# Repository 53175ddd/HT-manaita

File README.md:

# HT-manaita

Google の湯呑みキーボードの設計をもとに、それを展開して真魚板状にしました。  
派生元：<https://github.com/google/mozc-devices/tree/master/mozc-yunomi>

## 回路図

[Schematic](./img/HT-manaita.pdf)

## 画像

<div align="center">

</div>

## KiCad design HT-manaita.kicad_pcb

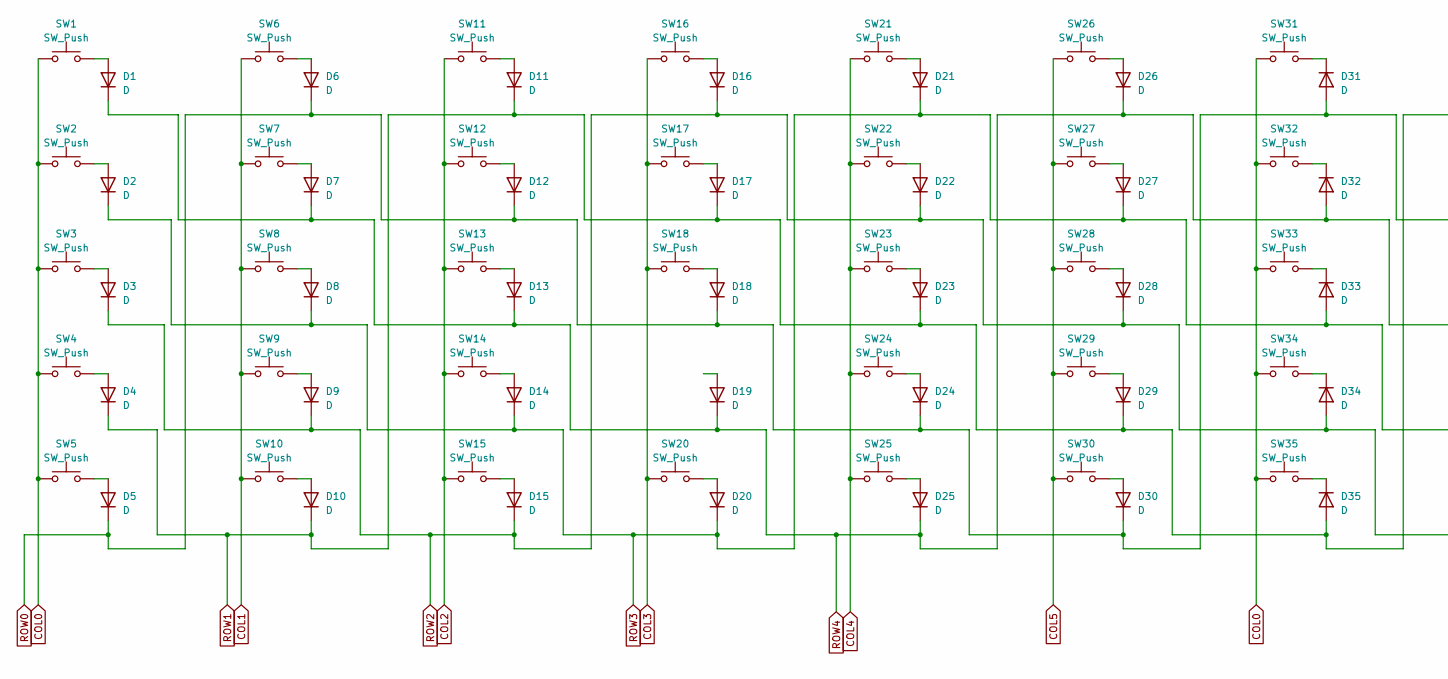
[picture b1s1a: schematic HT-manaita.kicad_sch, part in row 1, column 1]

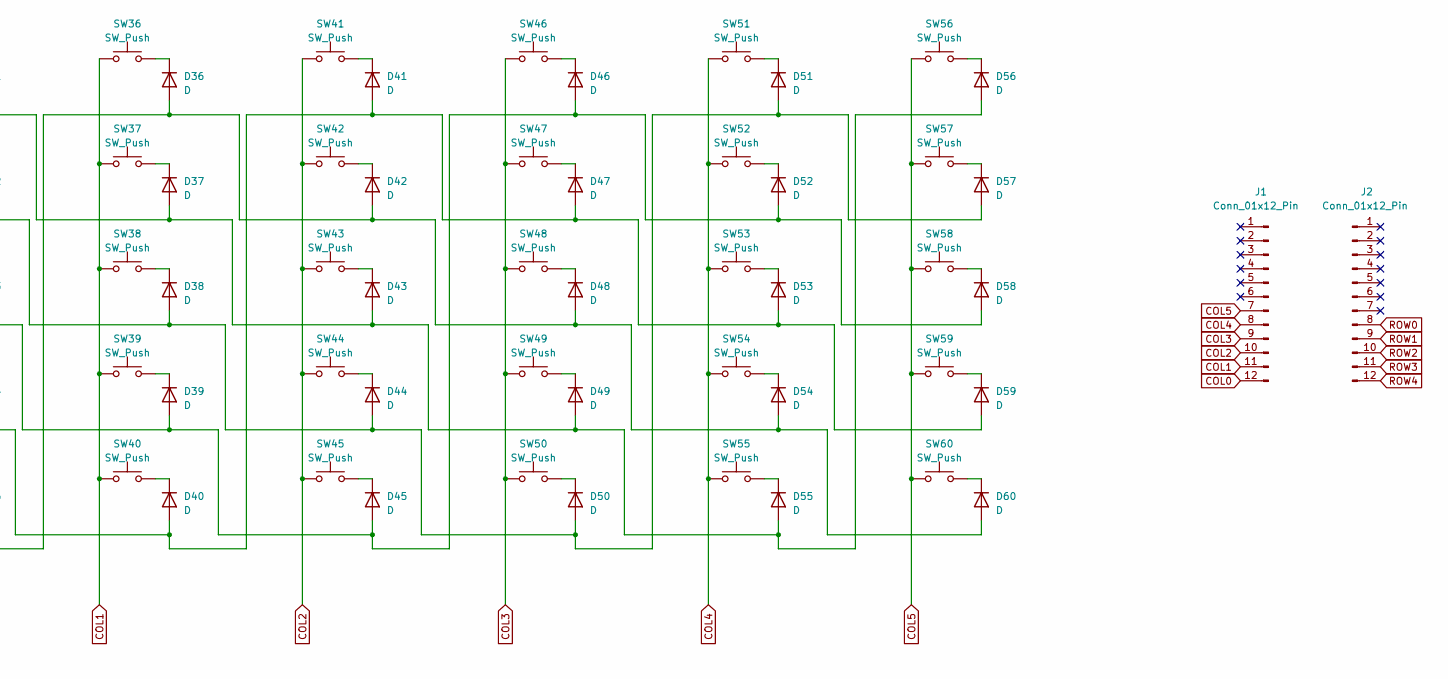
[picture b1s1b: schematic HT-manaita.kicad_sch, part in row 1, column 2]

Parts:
D1, D2, D3, D4, D5, D6, D7, D8, D9, D10, D11, D12, D13, D14, D15, D16, D17, D18, D19, D20, D21, D22, D23, D24, D25, D26, D27, D28, D29, D30, D31, D32, D33, D34, D35, D36, D37, D38, D39, D40, D41, D42, D43, D44, D45, D46, D47, D48, D49, D50, D51, D52, D53, D54, D55, D56, D57, D58, D59, D60: D; D_A-405_P10.16mm_Horizontal
J1, J2: Conn_01x12_Pin; PinHeader_1x12_P2.54mm_Vertical
SW1, SW2, SW3, SW4, SW5, SW6, SW7, SW8, SW9, SW10, SW11, SW12, SW13, SW14, SW15, SW16, SW17, SW18, SW20, SW21, SW22, SW23, SW24, SW25, SW26, SW27, SW28, SW29, SW30, SW31, SW32, SW33, SW34, SW35, SW36, SW37, SW38, SW39, SW40, SW41, SW42, SW43, SW44, SW45, SW46, SW47, SW48, SW49, SW50, SW51, SW52, SW53, SW54, SW55, SW56, SW57, SW58, SW59, SW60: SW_Push; SW_Cherry_MX_1.00u_PCB

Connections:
COL0: J1.12, SW1.1, SW2.1, SW3.1, SW4.1, SW5.1, SW31.1, SW32.1, SW33.1, SW34.1, SW35.1
COL1: J1.11, SW6.1, SW7.1, SW8.1, SW9.1, SW10.1, SW36.1, SW37.1, SW38.1, SW39.1, SW40.1
COL2: J1.10, SW11.1, SW12.1, SW13.1, SW14.1, SW15.1, SW41.1, SW42.1, SW43.1, SW44.1, SW45.1
COL3: J1.9, SW16.1, SW17.1, SW18.1, SW20.1, SW46.1, SW47.1, SW48.1, SW49.1, SW50.1
COL4: J1.8, SW21.1, SW22.1, SW23.1, SW24.1, SW25.1, SW51.1, SW52.1, SW53.1, SW54.1, SW55.1
COL5: J1.7, SW26.1, SW27.1, SW28.1, SW29.1, SW30.1, SW56.1, SW57.1, SW58.1, SW59.1, SW60.1
unnamed: D1.2 (A), SW1.2
unnamed: D2.2 (A), SW2.2
unnamed: D3.2 (A), SW3.2
unnamed: D4.2 (A), SW4.2
unnamed: D5.2 (A), SW5.2
unnamed: D6.2 (A), SW6.2
unnamed: D7.2 (A), SW7.2
unnamed: D8.2 (A), SW8.2
unnamed: D9.2 (A), SW9.2
unnamed: D10.2 (A), SW10.2
unnamed: D11.2 (A), SW11.2
unnamed: D12.2 (A), SW12.2
unnamed: D13.2 (A), SW13.2
unnamed: D14.2 (A), SW14.2
unnamed: D15.2 (A), SW15.2
unnamed: D16.2 (A), SW16.2
unnamed: D17.2 (A), SW17.2
unnamed: D18.2 (A), SW18.2
unnamed: D20.2 (A), SW20.2
unnamed: D21.2 (A), SW21.2
unnamed: D22.2 (A), SW22.2
unnamed: D23.2 (A), SW23.2
unnamed: D24.2 (A), SW24.2
unnamed: D25.2 (A), SW25.2
unnamed: D26.2 (A), SW26.2
unnamed: D27.2 (A), SW27.2
unnamed: D28.2 (A), SW28.2
unnamed: D29.2 (A), SW29.2
unnamed: D30.2 (A), SW30.2
unnamed: D31.1 (K), SW31.2
unnamed: D32.1 (K), SW32.2
unnamed: D33.1 (K), SW33.2
unnamed: D34.1 (K), SW34.2
unnamed: D35.1 (K), SW35.2
unnamed: D36.1 (K), SW36.2
unnamed: D37.1 (K), SW37.2
unnamed: D38.1 (K), SW38.2
unnamed: D39.1 (K), SW39.2
unnamed: D40.1 (K), SW40.2
unnamed: D41.1 (K), SW41.2
unnamed: D42.1 (K), SW42.2
unnamed: D43.1 (K), SW43.2
unnamed: D44.1 (K), SW44.2
unnamed: D45.1 (K), SW45.2
unnamed: D46.1 (K), SW46.2
unnamed: D47.1 (K), SW47.2
unnamed: D48.1 (K), SW48.2
unnamed: D49.1 (K), SW49.2
unnamed: D50.1 (K), SW50.2
unnamed: D51.1 (K), SW51.2
unnamed: D52.1 (K), SW52.2
unnamed: D53.1 (K), SW53.2
unnamed: D54.1 (K), SW54.2
unnamed: D55.1 (K), SW55.2
unnamed: D56.1 (K), SW56.2
unnamed: D57.1 (K), SW57.2
unnamed: D58.1 (K), SW58.2
unnamed: D59.1 (K), SW59.2
unnamed: D60.1 (K), SW60.2
ROW0: D5.1 (K), D6.1 (K), D12.1 (K), D18.1 (K), D24.1 (K), D30.1 (K), D31.2 (A), D37.2 (A), D43.2 (A), D49.2 (A), D55.2 (A), D56.2 (A), J2.8
ROW1: D4.1 (K), D10.1 (K), D11.1 (K), D17.1 (K), D23.1 (K), D29.1 (K), D35.2 (A), D36.2 (A), D42.2 (A), D48.2 (A), D54.2 (A), D60.2 (A), J2.9
ROW2: D3.1 (K), D9.1 (K), D15.1 (K), D16.1 (K), D22.1 (K), D28.1 (K), D34.2 (A), D40.2 (A), D41.2 (A), D47.2 (A), D53.2 (A), D59.2 (A), J2.10
ROW3: D2.1 (K), D8.1 (K), D14.1 (K), D20.1 (K), D21.1 (K), D27.1 (K), D33.2 (A), D39.2 (A), D45.2 (A), D46.2 (A), D52.2 (A), D58.2 (A), J2.11; also elsewhere on the board
ROW4: D1.1 (K), D7.1 (K), D13.1 (K), D19.1 (K), D25.1 (K), D26.1 (K), D32.2 (A), D38.2 (A), D44.2 (A), D50.2 (A), D51.2 (A), D57.2 (A), J2.12

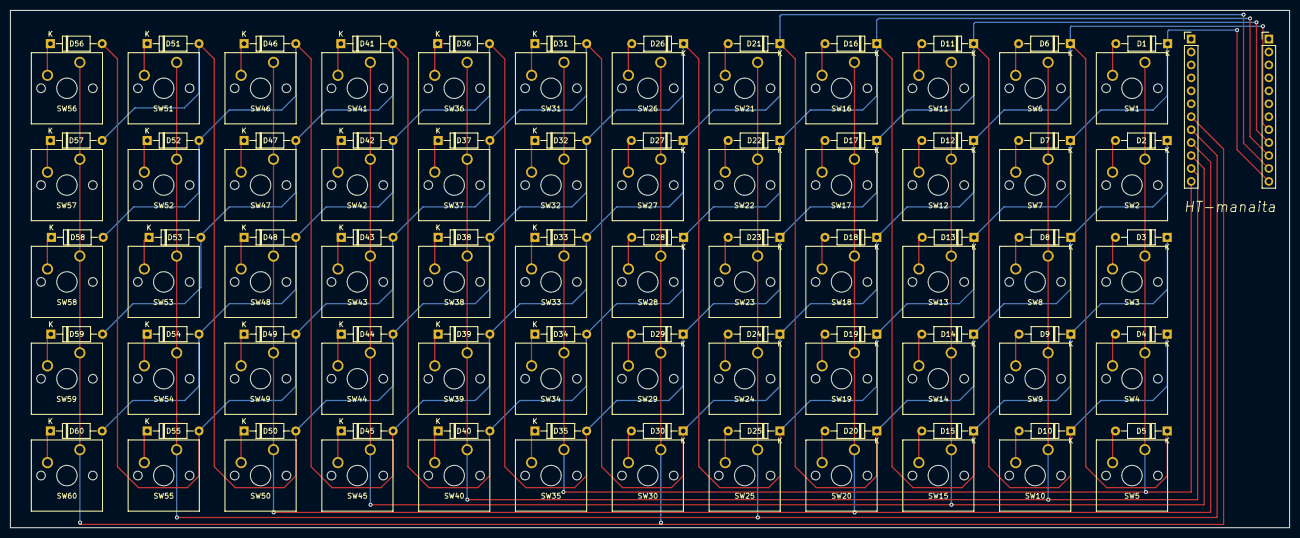
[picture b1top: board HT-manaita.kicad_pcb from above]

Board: 2 copper layers, 251.0 x 101.5 mm, 122 parts (0 on the bottom side), 70 nets.

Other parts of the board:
SW19: SW_Push; SW_Cherry_MX_1.00u_PCB

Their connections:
ROW3: SW19.1; also elsewhere on the board

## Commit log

2023-07-16 回路図作成
2023-07-16 部品配置・基板外形作成
2023-07-19 HT-manaita_v1.0 基板作成
2023-07-19 add images
2023-07-19 画像追加
2023-07-26 HT-manaita v1.1
2023-08-03 v2.0 アップデート
